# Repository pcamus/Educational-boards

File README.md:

## Educational prototyping boards.

In this repository, I will post prototyping boards I developed for my embedded systems courses.

- [Arduino thermostat shield](/Arduino_therm) : a shield used with Arduino mega to learn embedded programming.
- [Raspberry Pi Pico expansion board](/Pico_therm) : a board to plug a Pico and several peripherals.

My embedded programming textbook is avalaible : [Embedded_programming_220815.pdf](Embedded_programming_220815.pdf)

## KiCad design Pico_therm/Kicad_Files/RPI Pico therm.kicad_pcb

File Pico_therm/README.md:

## Raspberry Pi Pico thermostat experimentation board.

To teach how to use MicroPython with several peripherals, I developped a board with the following interfaces :

- RP2040 Pico socket.
- Thermostat interfaces:
  - An I2C LCD.
  - A DS18B20 temperature sensor.
  - A LDR.
  - A potentiometer.
  - A LED.
- A Neopixel header.
- An UART 0 Header.
- A µSD Header.

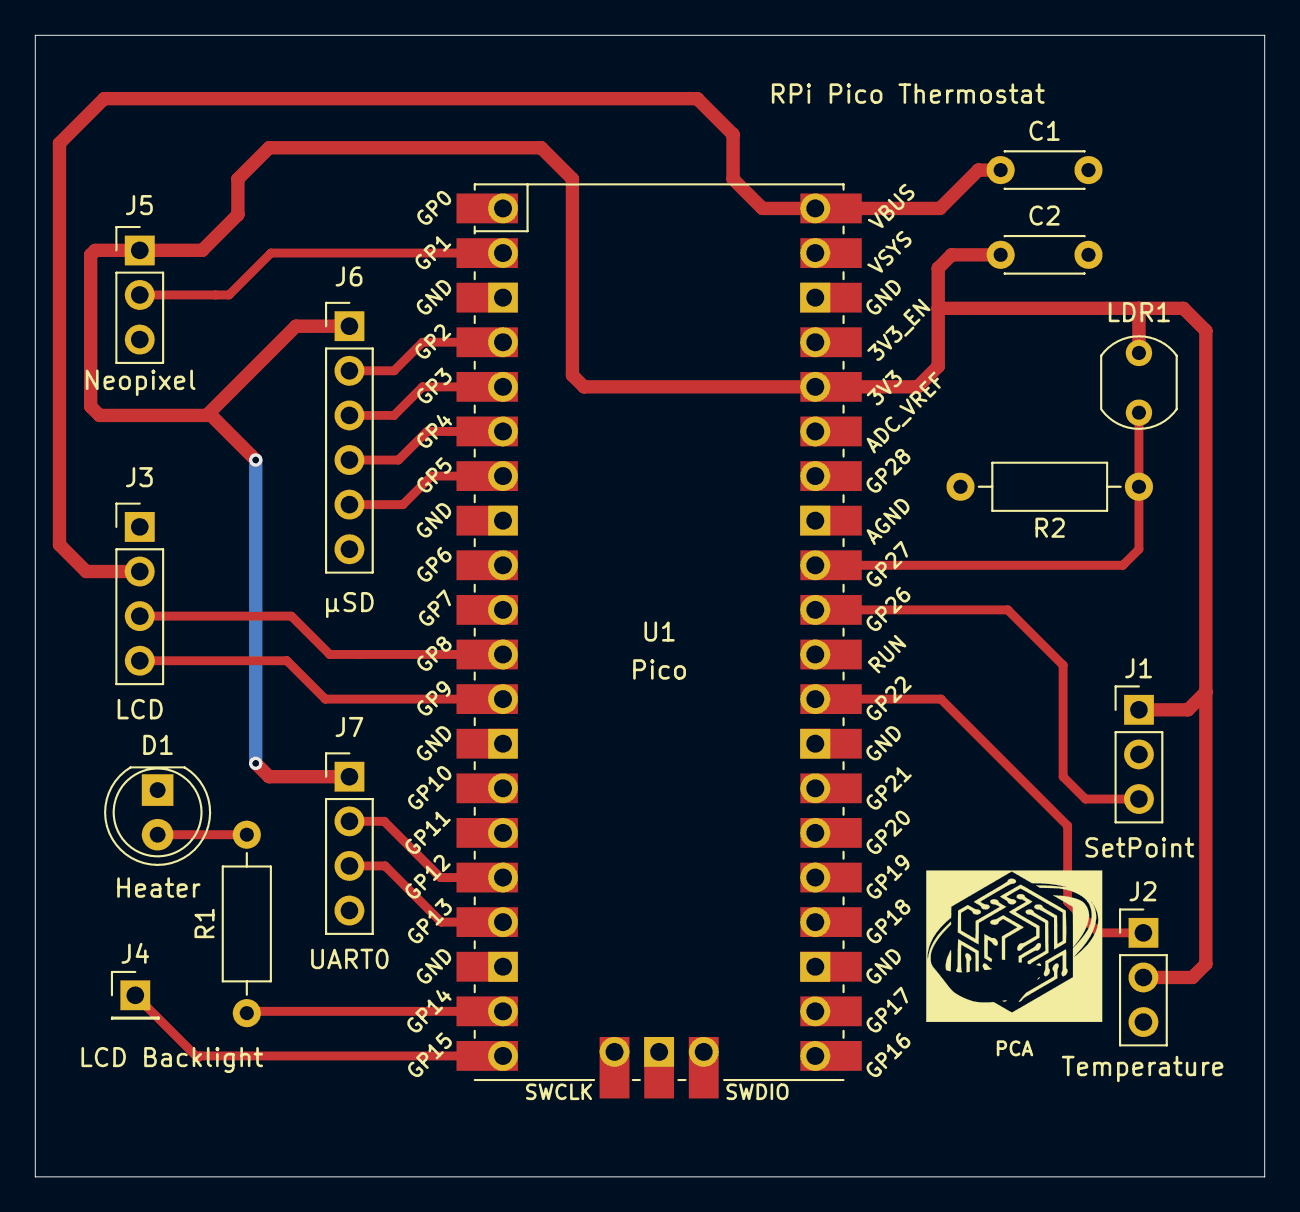
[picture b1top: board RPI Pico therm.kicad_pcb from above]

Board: 2 copper layers, 70.0 x 65.0 mm, 14 parts (0 on the bottom side), 18 nets.

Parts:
C1, C2: 100nF; C_Disc_D4.3mm_W1.9mm_P5.00mm
D1: LED; LED_D5.0mm
J1: SetPoint; PinHeader_1x03_P2.54mm_Vertical
J2: Temperature; PinHeader_1x03_P2.54mm_Vertical
J3: LCD; PinHeader_1x04_P2.54mm_Vertical
J4: LCD Backlight; PinHeader_1x01_P2.54mm_Vertical
J5: Neopixel; PinHeader_1x03_P2.54mm_Vertical
J6: µSD; PinHeader_1x06_P2.54mm_Vertical
J7: UART0; PinHeader_1x04_P2.54mm_Vertical
LDR1: LDR07; R_LDR_5.1x4.3mm_P3.4mm_Vertical
R1: 560R; R_Axial_DIN0207_L6.3mm_D2.5mm_P10.16mm_Horizontal
R2: 10k; R_Axial_DIN0207_L6.3mm_D2.5mm_P10.16mm_Horizontal
U1: Pico; RPi_Pico_SMD_TH

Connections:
+3V3: C2.1, J1.1, J2.2, J5.1, J6.1, J7.1, LDR1.1, U1.36
+5V: C1.1, J3.2, U1.40
/Bckl: J4.1, U1.20
/CSn: J6.5, U1.7
/Heater: R1.1, U1.19
/LDR: LDR1.2, R2.1, U1.32
/MISO: J6.4, U1.6
/MOSI: J6.3, U1.5
/Neopix: J5.2, U1.2
/Onewire: J2.1, U1.29
/POT: J1.3, U1.31
/RxD0: J7.3, U1.17
/SCK: J6.2, U1.4
/SCL: J3.4, U1.12
/SDA: J3.3, U1.11
/TxD0: J7.2, U1.16
GND: C1.2, C2.2, D1.1, J1.2, J2.3, J3.1, J5.3, J6.6, J7.4, R2.2, U1.3, U1.8, U1.13, U1.18, U1.23, U1.28, U1.33, U1.38
unnamed: D1.2, R1.2

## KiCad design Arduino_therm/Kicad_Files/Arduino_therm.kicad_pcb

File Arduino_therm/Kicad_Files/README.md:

## Kicad files version 5

Schematic and PCB also available in pdf format.

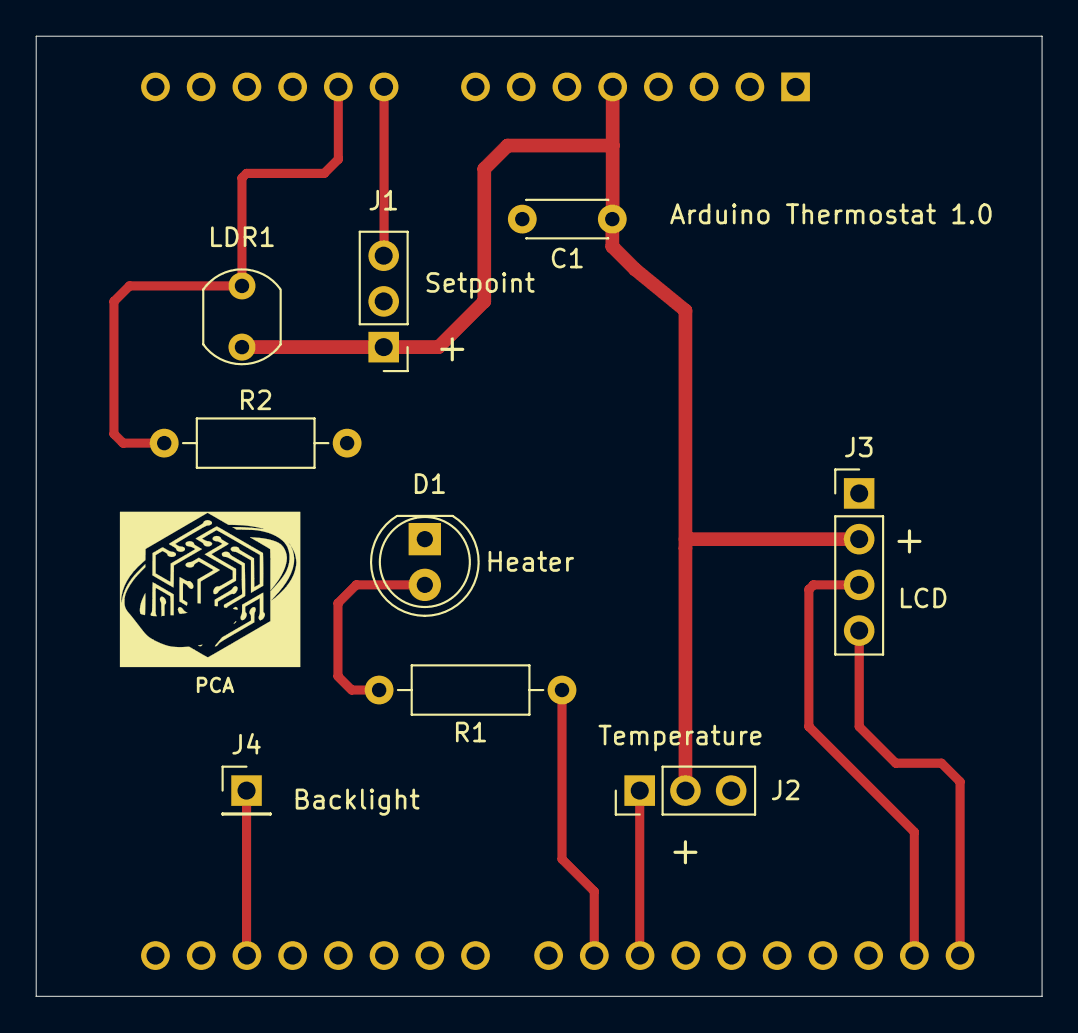
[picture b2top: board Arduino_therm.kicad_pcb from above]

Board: 2 copper layers, 55.9 x 53.3 mm, 10 parts (0 on the bottom side), 10 nets.

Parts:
A1: Arduino_UNO_R3; Arduino_UNO_R3_topv
C1: 100 nF; C_Disc_D4.3mm_W1.9mm_P5.00mm
D1: LED; LED_D5.0mm
J1: Setpoint; PinHeader_1x03_P2.54mm_Vertical
J2: Temperature; PinHeader_1x03_P2.54mm_Vertical
J3: LCD; PinHeader_1x04_P2.54mm_Vertical
J4: LCD Backlight; PinHeader_1x01_P2.54mm_Vertical
LDR1: LDR07; R_LDR_5.1x4.3mm_P3.4mm_Vertical
R1: 820R; R_Axial_DIN0207_L6.3mm_D2.5mm_P10.16mm_Horizontal
R2: 10k; R_Axial_DIN0207_L6.3mm_D2.5mm_P10.16mm_Horizontal

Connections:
/Backlight: A1.17, J4.1
/Heater: A1.24, R1.1
/LDR: A1.10, LDR1.2, R2.1
/Onewire: A1.25, J2.1
/POT: A1.9, J1.3
/SCL: A1.32, J3.4
/SDA: A1.31, J3.3
GND: A1.6, A1.7, A1.29, C1.2, D1.1, J1.2, J2.3, J3.1, R2.2
unnamed: D1.2, R1.2
VCC: A1.5, C1.1, J1.1, J2.2, J3.2, LDR1.1

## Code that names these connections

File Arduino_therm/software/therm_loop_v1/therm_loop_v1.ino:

/**
 * @file therm_loop_v1.ino
 * @brief  thermostat
 * Uses therm_loop_util_v1.ino for functions code
 * @author philippe.camus@hepl.be 
 * @date 19/8/2021   
 */
 
// Necessary libraries 
#include <Wire.h> 
#include <LiquidCrystal_I2C.h>
#include <OneWire.h>
#include <DallasTemperature.h>

#define HEATER_LED 9
#define DS18B20_PIN 10
#define POT A0
#define LDR A1
#define BACKLIGHT 2
#define ON 1
#define OFF 0

#define PROBE 13 // to check loop timing

//#define DEBUG // in normal mode comment out this line
 
// create I/O objects
LiquidCrystal_I2C lcd(0x27,20,2);  // set the LCD address to 0x27 for a 16 chars and 2 line display
OneWire oneWire(DS18B20_PIN); // set up oneWire to pin 10 (DS18B20 connection)
DallasTemperature sensors(&oneWire); // create a DS18B20 object

#include "therm_loop_util_v1.h" // header for your functions


// the setup function runs once when you press reset or power the board
void setup() 
{
#ifdef DEBUG
// initialize console serial communication at 9600 bits per second:
Serial.begin(9600);
#endif

//hardware initialization sensors, display, output controler...
hardware_setup();

pinMode(PROBE, OUTPUT);
digitalWrite(PROBE, LOW);
}


// run continuously
void loop()
{  
uint16_t temperature;
uint16_t setpoint;
uint16_t luminosity;

digitalWrite(PROBE, HIGH);// 1 level = loop duration
  
temperature = read_temperature(); 
display_temperature(temperature);

setpoint = read_setpoint(); 
display_setpoint(setpoint);

if (temperature < setpoint)
  set_heater(ON);
 else
  set_heater(OFF);
   
luminosity = read_luminosity(); 
display_luminosity(luminosity); 

digitalWrite(PROBE, LOW);

delay(500);
#ifdef DEBUG
Serial.println("");
#endif
}

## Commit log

2022-08-04 Create KiCad files
2022-11-16 Corrected to remove global variables
2022-11-22 Add roadworks traffic lights
